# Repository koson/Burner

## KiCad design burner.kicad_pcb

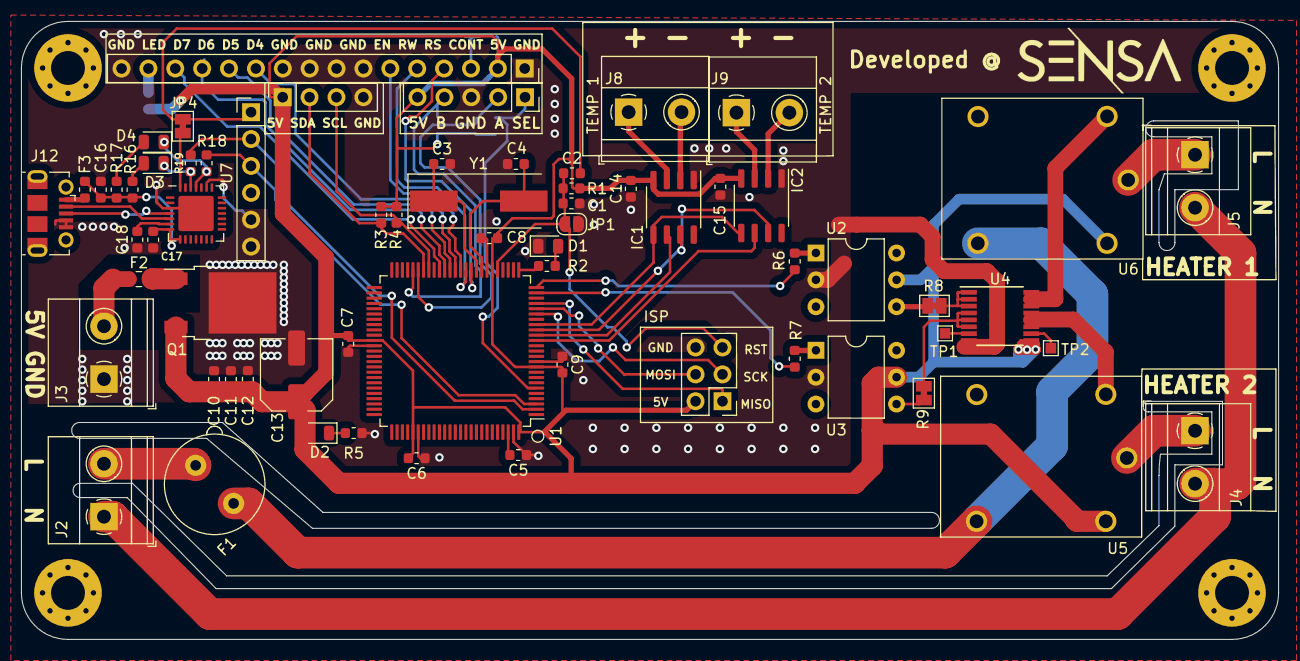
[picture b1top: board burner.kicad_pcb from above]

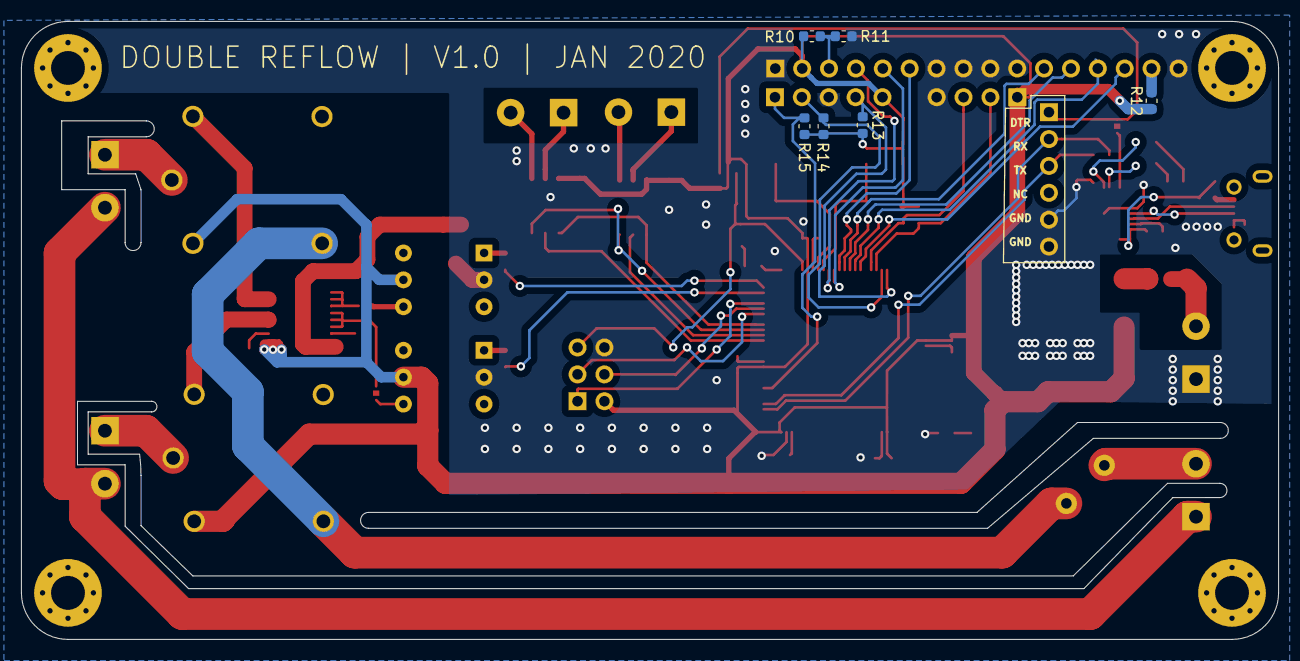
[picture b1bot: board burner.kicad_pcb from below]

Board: 2 copper layers, 118.8 x 58.4 mm, 75 parts (6 on the bottom side), 66 nets.

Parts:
C1, C2, C5, C6, C7, C8, C9, C10, C14, C15, C16, C17, C18: 100nF; C_0603_1608Metric
C3, C4: 22pF; C_0603_1608Metric
C11: 1uF; C_0603_1608Metric
C12: 10uF; C_0603_1608Metric
C13: 100uF; C_Elec_6.3x5.4
D1, D2, D3, D4: LED; LED_0805_2012Metric
F1: Fuse; Fuseholder_TR5_Littelfuse_No560_No460
F2: Fuse; Fuse_0805_2012Metric
F3: Fuse; Fuse_0603_1608Metric
H1, H3, H4, H5: MountingHole; MountingHole_3.2mm_M3_Pad_Via
IC1, IC2: MAX6675; SO-8_3.9x4.9mm_P1.27mm
J1: MCU_ISP; PinHeader_2x03_P2.54mm_Vertical
J2: 220V_INPUT; TerminalBlock_Phoenix_MKDS-1,5-2_1x02_P5.00mm_Horizontal
J3: 5V_INPUT; TerminalBlock_Phoenix_MKDS-1,5-2_1x02_P5.00mm_Horizontal
J4: BURNER2; TerminalBlock_Phoenix_MKDS-1,5-2_1x02_P5.00mm_Horizontal
J5: BURNER1; TerminalBlock_Phoenix_MKDS-1,5-2_1x02_P5.00mm_Horizontal
J6: 1604_conn; PinSocket_1x16_P2.54mm_Vertical
J7: I2C_DISPLAY; PinSocket_1x04_P2.54mm_Vertical
J8, J9: KTYPE1; TerminalBlock_Phoenix_MKDS-1,5-2_1x02_P5.00mm_Horizontal
J12: USB_A; USB_Micro-B_Molex-105017-0001
J13: FTDI; PinHeader_1x06_P2.54mm_Vertical
J14: ENCODER; PinSocket_1x05_P2.54mm_Vertical
JP1: RESET; SolderJumper-2_P1.3mm_Open_RoundedPad1.0x1.5mm
JP4: JUMPER; SolderJumper-2_P1.3mm_Bridged_Pad1.0x1.5mm
Q1: AOD417; TO-252-2
R1, R2, R13, R14, R15: 10k; R_0603_1608Metric
R3, R4, R10: 4k7; R_0603_1608Metric
R5, R16, R17, R18, R19: 1k; R_0603_1608Metric
R6, R7: 330; R_0603_1608Metric
R8, R9: 0; SolderJumper-2_P1.3mm_Bridged_Pad1.0x1.5mm
R11, R12: 1k6; R_0603_1608Metric
TP1, TP2: TestPoint; TestPoint_Pad_1.0x1.0mm
U1: ATmega2560-16AU; TQFP-100_14x14mm_P0.5mm
U2, U3: 4N25; DIP-6_W7.62mm
U4: ULN2003A; TSSOP-16_4.4x5mm_P0.65mm
U5, U6: AZ943
U7: CP2102N-A01-GQFN28; QFN-28-1EP_5x5mm_P0.5mm_EP3.35x3.35mm
Y1: 16MHz; Crystal_SMD_HC49-SD

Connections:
+5V: C6.2, C7.2, C8.2, C9.2, C10.1, C11.1, C12.1, C13.1, C14.1, C15.1, D2.2, IC1.4, IC2.4, J1.2, J6.2, J7.1, J14.5, Q1.3, R1.1, R3.2, R4.1, R10.2, R12.1, R13.2, R14.2, R15.2, U1.10, U1.31, U1.61, U1.80, U1.100, U2.5, U3.5, U4.9, U5.2, U6.2
+5VA: C16.2, C17.1, F3.1, R16.2, R17.2, U7.7, U7.8
/Relay/220V_L: F1.1, U5.3, U6.3
/Relay/220V_N: J2.1, J4.2, J5.2
CP_D+: J12.3, U7.4
CP_D-: J12.2, U7.5
CP_DTR: JP4.1, U7.28
CP_RX: D4.1, R18.1, U7.25
CP_TX: D3.1, R19.1, U7.26
DISP_1604_D4: J6.11, U1.38
DISP_1604_D5: J6.12, U1.39
DISP_1604_D6: J6.13, U1.40
DISP_1604_D7: J6.14, U1.41
DISP_1604_EN: J6.6, U1.37
DISP_1604_RS: J6.4, U1.35
DISP_1604_RW: J6.5, U1.36
DISP_ENC_A: J14.2, R14.1, U1.45
DISP_ENC_B: J14.4, R13.1, U1.46
DISP_ENC_SEL: J14.1, R15.1, U1.6
GND: C1.1, C3.2, C4.2, C5.1, C6.1, C7.1, C8.1, C9.1, C10.2, C11.2, C12.2, C13.2, C14.2, C15.2, C16.1, C17.2, C18.1, D1.1, IC1.1, IC2.1, J1.6, J3.1, J6.1, J6.7, J6.8, J6.9, J6.10, J6.16, J7.4, J12.4, J12.5, J13.5, J13.6, J14.3, JP1.2, Q1.2, R5.2, R11.1, U1.11, U1.32, U1.62, U1.81, U1.99, U2.2, U3.2, U4.8, U7.3, U7.29
MCU_DTR: C2.2, J13.1, JP4.2
MCU_ISP_MISO: J1.1, U1.22
MCU_ISP_MOSI: J1.4, U1.21
MCU_ISP_SCK: J1.3, U1.20
MCU_RST: C1.2, C2.1, J1.5, JP1.1, R1.2, U1.30
MCU_RX: J13.2, R19.2, U1.2
MCU_SCL: J7.3, R4.2, U1.43
MCU_SDA: J7.2, R3.1, U1.44
MCU_TX: J13.3, R18.2, U1.3
unnamed: C3.1, U1.34, Y1.1
unnamed: C4.1, U1.33, Y1.2
unnamed: C5.2, U1.98
unnamed: C18.2, U7.6
unnamed: D1.2, R2.1
unnamed: D2.1, R5.1
unnamed: D3.2, R16.1
unnamed: D4.2, R17.1
unnamed: F1.2, J2.2
unnamed: F2.1, Q1.1
unnamed: F2.2, J3.2
unnamed: F3.2, J12.1
unnamed: IC1.2, J8.2
unnamed: IC1.3, J8.1
unnamed: IC2.2, J9.2
unnamed: IC2.3, J9.1
unnamed: J4.1, U5.1
unnamed: J5.1, U6.1
unnamed: J6.3, R10.1, R11.2
unnamed: J6.15, R12.2
unnamed: R2.2, U1.26
unnamed: R6.1, U2.1
unnamed: R7.1, U3.1
unnamed: R8.1, U4.1, U4.2, U4.3
unnamed: R8.2, U2.4
unnamed: R9.1, U4.4, U4.5, U4.6
unnamed: R9.2, U3.4
unnamed: TP1.1, U4.7
unnamed: TP2.1, U4.10
unnamed: U4.11, U4.12, U4.13, U5.5
unnamed: U4.14, U4.15, U4.16, U6.5
RELAY_1: R6.2, U1.25
RELAY_2: R7.2, U1.24
TEMP_MAX_CS1: IC1.6, U1.16
TEMP_MAX_CS2: IC2.6, U1.15
TEMP_MAX_SCK: IC1.5, IC2.5, U1.18
TEMP_MAX_SO: IC1.7, IC2.7, U1.17

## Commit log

2020-01-25 finished board
2020-01-25 added schematic
2020-01-25 added 3d to k type
